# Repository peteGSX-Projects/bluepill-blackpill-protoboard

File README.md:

# Prototyping boards for STM32F103C8 Bluepill and STM32F411CE Blackpill

This repo contains the KiCad files for a prototyping board for both the STM32F103C8 Bluepill and STM32F411CE Blackpill boards.

These have been designed by a complete amateur with absolutly no knowledge of power supplies, and therefore these are a best effort design using recommended components and circuit designs for the power supply.

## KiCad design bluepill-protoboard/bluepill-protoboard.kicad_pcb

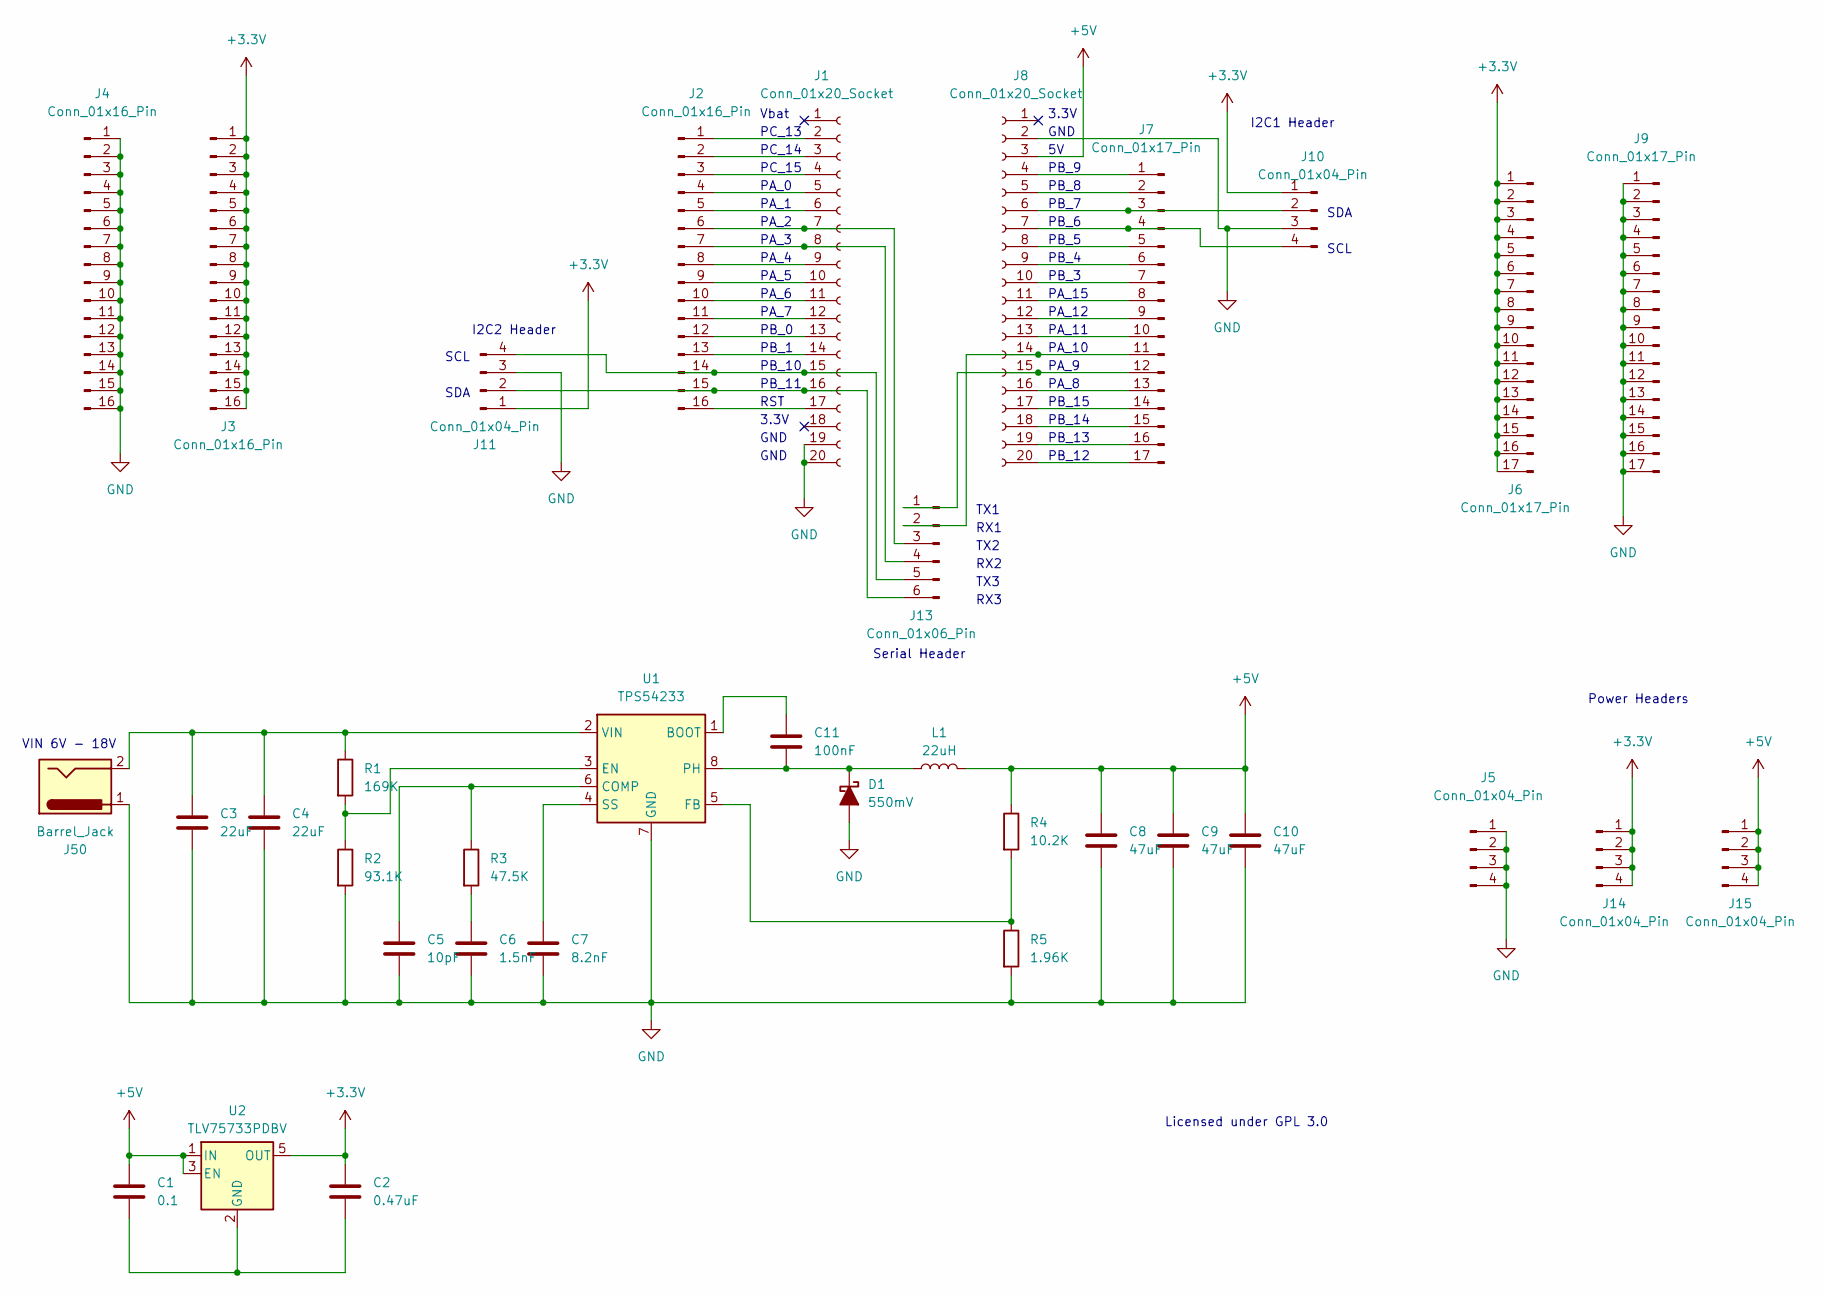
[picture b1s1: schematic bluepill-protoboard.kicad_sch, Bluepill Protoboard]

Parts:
C1: 0.1; C_0402_1005Metric
C2: 0.47uF; C_0402_1005Metric
C3, C4: 22uF; C_0402_1005Metric
C5: 10pF; C_0402_1005Metric
C6: 1.5nF; C_0402_1005Metric
C7: 8.2nF; C_0402_1005Metric
C8, C9, C10: 47uF; C_0402_1005Metric
C11: 100nF; C_0402_1005Metric
D1: 550mV; D_01005_0402Metric
J1, J8: Conn_01x20_Socket; PinSocket_1x20_P2.54mm_Vertical
J2, J3, J4: Conn_01x16_Pin; PinHeader_1x16_P2.54mm_Vertical
J5, J10, J11, J14, J15: Conn_01x04_Pin; PinHeader_1x04_P2.54mm_Vertical
J6, J7, J9: Conn_01x17_Pin; PinHeader_1x17_P2.54mm_Vertical
J13: Conn_01x06_Pin; PinHeader_1x06_P2.54mm_Vertical
J50: Barrel_Jack; BarrelJack_Horizontal
L1: 22uH; L_0402_1005Metric
R1: 169K; R_0402_1005Metric
R2: 93.1K; R_0402_1005Metric
R3: 47.5K; R_0402_1005Metric
R4: 10.2K; R_0402_1005Metric
R5: 1.96K; R_0402_1005Metric
U1: TPS54233; SOIC-8_3.9x4.9mm_P1.27mm
U2: TLV75733PDBV; SOT-23-5

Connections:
+3.3V: C2.1, J3.1, J3.2, J3.3, J3.4, J3.5, J3.6, J3.7, J3.8, J3.9, J3.10, J3.11, J3.12, J3.13, J3.14, J3.15, J3.16, J6.1, J6.2, J6.3, J6.4, J6.5, J6.6, J6.7, J6.8, J6.9, J6.10, J6.11, J6.12, J6.13, J6.14, J6.15, J6.16, J6.17, J10.1, J11.1, J14.1, J14.2, J14.3, J14.4, U2.5 (OUT)
+5V: C1.1, C8.1, C9.1, C10.1, J8.3, J15.1, J15.2, J15.3, J15.4, L1.2, R4.1, U2.1 (IN), U2.3 (EN)
GND: C3.2, C4.2, C5.2, C6.2, C7.2, C8.2, C9.2, C10.2, D1.2 (A), J1.19, J1.20, J4.1, J4.2, J4.3, J4.4, J4.5, J4.6, J4.7, J4.8, J4.9, J4.10, J4.11, J4.12, J4.13, J4.14, J4.15, J4.16, J5.1, J5.2, J5.3, J5.4, J8.2, J9.1, J9.2, J9.3, J9.4, J9.5, J9.6, J9.7, J9.8, J9.9, J9.10, J9.11, J9.12, J9.13, J9.14, J9.15, J9.16, J9.17, J10.3, J11.3, J50.1, R2.2, R5.2, U1.7 (GND)
unnamed: C6.1, R3.2
unnamed: C11.2, D1.1 (K), L1.1, U1.8 (PH)
unnamed: J1.2, J2.1
unnamed: J1.3, J2.2
unnamed: J1.4, J2.3
unnamed: J1.5, J2.4
unnamed: J1.6, J2.5
unnamed: J1.7, J2.6, J13.3
unnamed: J1.8, J2.7, J13.4
unnamed: J1.9, J2.8
unnamed: J1.10, J2.9
unnamed: J1.11, J2.10
unnamed: J1.12, J2.11
unnamed: J1.13, J2.12
unnamed: J1.14, J2.13
unnamed: J1.15, J2.14, J11.4, J13.5
unnamed: J1.16, J2.15, J11.2, J13.6
unnamed: J1.17, J2.16
unnamed: J7.1, J8.4
unnamed: J7.2, J8.5
unnamed: J7.5, J8.8
unnamed: J7.6, J8.9
unnamed: J7.7, J8.10
unnamed: J7.8, J8.11
unnamed: J7.9, J8.12
unnamed: J7.10, J8.13
unnamed: J7.13, J8.16
unnamed: J7.14, J8.17
unnamed: J7.15, J8.18
unnamed: J7.16, J8.19
unnamed: J7.17, J8.20
unnamed: J7.3, J8.6, J10.2
unnamed: J7.4, J8.7, J10.4
unnamed: J7.12, J8.15, J13.1
unnamed: J7.11, J8.14, J13.2
unnamed: C11.1, U1.1 (BOOT)
unnamed: C5.1, R3.1, U1.6 (COMP)
unnamed: R1.2, R2.1, U1.3 (EN)
unnamed: R4.2, R5.1, U1.5 (FB)
unnamed: C7.1, U1.4 (SS)
unnamed: C3.1, C4.1, J50.2, R1.1, U1.2 (VIN)
unnamed: C1.2, C2.2, U2.2 (GND)

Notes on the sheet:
Licensed under GPL 3.0
GND
PC_15
TX1
PA_1
PA_6
PB_10
PA_5
3.3V
PA_8
RX2
PB_11
RX3
Power Headers
PB_8
PB_14
PB_5
RST
PA_10
PA_12
SCL
PA_0
PA_15
PA_11
SDA
PB_4
PC_14
PC_13
PB_7
I2C2 Header
PA_7
Vbat
Serial Header
PB_6
PB_3
RX1
PB_13
VIN 6V - 18V
PA_3
I2C1 Header

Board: 2 copper layers, 35 parts (0 on the bottom side), 45 nets, no tracks yet.

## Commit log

2023-09-25 Update gitignore
2023-09-25 Schematic start
2023-09-26 Headers done
2023-09-26 Add license
2023-09-26 Add pin labels
2023-09-27 Add regulator drafts
2023-09-27 Add missed connections
2023-09-27 Relocate ground
2023-09-30 Update components
2023-10-04 Start PCB
2023-10-05 More PCB
